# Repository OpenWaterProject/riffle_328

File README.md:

#Welcome!

This is a set of code and instructions for getting started with the Riffle_328 water monitor, version 0.1.8. 

- **QUICK START**.   If you already have experience using Arduino-compatible boards, you should probably just jump to the [Quick Start](https://github.com/dwblair/Riffle-Getting-Started#quick-start) section below to get up and running quickly. In general, the Riffle behaves like an Arduino UNO in the Arduino IDE (you should select "Arduino UNO" as the "Board" in the IDE), but you'll need to install a **special driver** (see [Software prep](test), below) in order to program the device over USB if you're using Mac or Windows.  

- **STEP-BY-STEP**.  If you would prefer more detailed instructions for setting up your Riffle, please check out the [Step-by-Step Instructions](./step-by-step.markdown).

- **EXAMPLES**. If you'd like to try out some example Riffle sensor applications (temperature, pressure, etc) in the [wiki](https://github.com/dwblair/Riffle-Getting-Started/wiki) of this repository (add your own!).

- **DESIGN PHILOSOPHY**.  A brief description of the motivation behind the design of the Riffle can be found [here](https://github.com/OpenWaterProject/riffle/blob/master/design_philosophy.md).  

# How you can contribute

Some useful guidelines about the best way to contribute to the project (or to fork it) can be found [here](contributing.md).

# Support and Licensing 

The Riffle_328 project has been supported through [Public Lab](www.publiclab.org)'s Open Water Initiative, and is licensed under [CERN OHL 1.2](LiCENSE.md).

# Quick Overview

**Hardware notes**.  This repository contains the design files and Bill of Materials for the Riffle water monitor.  The Riffle_328 is directly compatible with the Arduino IDE (it can be programmed as an "Arduino UNO" board).  The Riffle_328 ver 0.1.8 has the following features:

- Programmed as an "UNO" in the Arduino IDE
- Uses an Atmel 328p chip, running at 16 MHz and 3.3V.
- On-board microSD card
- On-board Serial-USB conversion using the CH340 chip.
- Battery measurement circuit
- High-precision, temperature-compensated RTC, the DS3221, with a CR1220 backup battery to maintain the time.
- Two power inputs, 3.5 - 6V.  -- one allows for Lithium-Ion charging when the Riffle is plugged into USB, the other is for extended, low-power operation. 
- It has additional on-board EEPROM memory, accessible via the I2C bus.
- It has MOSFET switches that can power down the microSD card, the external sensor power, and the battery measurement circuitry. 
- Analog pins, Digital pins, Power, Ground, Battery voltage, and I2C and SPI buses are broken out on a 2x7 header at the end of the board, as follows:

**Versions of the Riffle**. [Ben Gamari](https://github.com/bgamari)'s original [Riffle design](https://github.com/bgamari/riffle) is based on an ARM Cortex-M4 chip, the Kinetis K20.  The K20 is a more powerful chip than the Atmel 328, but the K20 version of the Riffle doesn't currently have firmware compatible with the Arduino IDE.  The Riffle_328 design covered in this repository is intended to be as directly compatible with the Arduino IDE as possible.

**Finding more resources**. The Riffle has been developed through many contributions by members of the [Public Lab](http://publiclab.org) community.  For more information, see:

- The main [Public Lab Riffle wiki](https://publiclab.org/wiki/riffle);
- All [posts and research notes](https://publiclab.org/search/riffle) related to the Riffle on Public Lab;
- The [Public Lab Water Quality Mailing list](https://groups.google.com/forum/#!forum/plots-waterquality).

# Quick Start

## Hardware prep

- For basic datalogging, ou'll need a Riffle board, a 3-6 volt battery (3.7 V Lithium Ion battery shown), and CR1220 coin cell battery.  Protoboards (shown) are optional. 

- Insert a microSD card and a CR1220 coin cell into the appropriate slots on the Riffle.

- The Riffle 328 ver 0.1.8 has two JST connectors for power inputs, a switch to choose between the two power inputs, and an indicator LED in the middle of the board (connected to pin 9):

- Insert a lithium ion battery into the 'Lith/USB' JST connector (JST connector labels are on the back side of the board).

- Make sure that the switch on the Riffle is switched to the side labeled 'Lith/USB' (label is next to switch).

- When you're done, your setup should look like this:

## Software prep

- Make sure that the Arduino IDE (version 1.6.10 or higher) is installed.  If it
 isn't, get it [here](https://www.arduino.cc/en/Main/Software).

- **Installing the USB-Serial Driver**. On Mac or Windows, the Riffle requires a special driver in order to be programmed via the Arduino IDE, due to the onbaord CH340 USB-Serial chip.  For Windows, you can use the driver [here]( http://raysfiles.com/drivers/ch341ser.exe).  For Mac, follow instructions [here]( http://www.instructables.com/id/Arduino-Nano-CH340/). Linux systems should generally not require additional drivers.

- Copy all of the folders in 'arduino_libraries' into the 'libraries' folder inside the 'sketchbook' folder associated with the Arduino IDE install.  These libraries are necessary for running the 'temp_logger.ino' and 'set_rtc.ino' sketches in this repo.  

## Logging values to the microSD card

- Using the Arduino IDE, compile the 'temp_logger.ino' code from the "example_sketches" folder in this repo, and load it onto the Riffle board, using 'Arduino UNO' as the 'Board' version in the Arduino IDE.

- The Riffle should start logging temperature values to the microSD card. These temperature values come from the on-board RTC, and so may be affected by the temeprature of the board (which might slightly higher than ambient temperature, due to the operation of its circuitry). 

- Note: the RTC will have its time set automatically to the system clock when it is programmed via the Arduino IDE.

## Extending the battery lifetime

- Set DEBUG = 0 in temp_logger.ino. This will reduce power by turning off the Serial interface.  It will also mean that the RTC is not set by the System clock.

- Use the 'GEN' JST connector on the Riffle board.  This power input doesn't have a protective diode, thus avoiding a diode-associated voltage drop, and can power the Riffle down to lower battery voltages.

- Test out different microSD cards;  some of them 'sleep' at lower power settings than others.

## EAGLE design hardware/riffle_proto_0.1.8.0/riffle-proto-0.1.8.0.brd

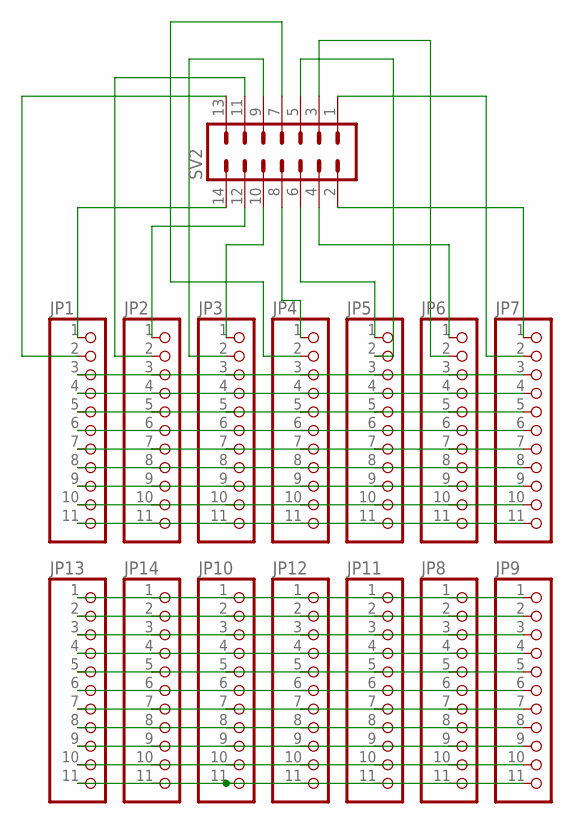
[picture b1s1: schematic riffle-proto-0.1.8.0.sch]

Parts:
JP1, JP2, JP3, JP4, JP5, JP6, JP7, JP8, JP9, JP10, JP11, JP12, JP13, JP14: HEADER-1X1176MIL; 1X11_ROUND_76
SV2: MA07-2

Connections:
unnamed: JP1.1, SV2.14
unnamed: JP2.1, SV2.12
unnamed: JP3.1, SV2.10
unnamed: JP4.1, SV2.8
unnamed: JP5.1, SV2.6
unnamed: JP6.1, SV2.4
unnamed: JP7.1, SV2.2
unnamed: JP1.2, SV2.13
unnamed: JP2.2, SV2.11
unnamed: JP3.2, SV2.9
unnamed: JP4.2, SV2.7
unnamed: JP5.2, SV2.5
unnamed: JP6.2, SV2.3
unnamed: JP7.2, SV2.1
unnamed: JP1.3, JP2.3, JP3.3, JP4.3, JP5.3, JP6.3, JP7.3
unnamed: JP1.4, JP2.4, JP3.4, JP4.4, JP5.4, JP6.4, JP7.4
unnamed: JP1.5, JP2.5, JP3.5, JP4.5, JP5.5, JP6.5, JP7.5
unnamed: JP1.6, JP2.6, JP3.6, JP4.6, JP5.6, JP6.6, JP7.6
unnamed: JP1.7, JP2.7, JP3.7, JP4.7, JP5.7, JP6.7, JP7.7
unnamed: JP1.8, JP2.8, JP3.8, JP4.8, JP5.8, JP6.8, JP7.8
unnamed: JP1.9, JP2.9, JP3.9, JP4.9, JP5.9, JP6.9, JP7.9
unnamed: JP1.10, JP2.10, JP3.10, JP4.10, JP5.10, JP6.10, JP7.10
unnamed: JP1.11, JP2.11, JP4.11, JP5.11, JP6.11, JP7.11
unnamed: JP8.1, JP9.1, JP10.1, JP11.1, JP12.1, JP13.1, JP14.1
unnamed: JP8.2, JP9.2, JP10.2, JP11.2, JP12.2, JP13.2, JP14.2
unnamed: JP8.3, JP9.3, JP10.3, JP11.3, JP12.3, JP13.3, JP14.3
unnamed: JP8.4, JP9.4, JP10.4, JP11.4, JP12.4, JP13.4, JP14.4
unnamed: JP8.5, JP9.5, JP10.5, JP11.5, JP12.5, JP13.5, JP14.5
unnamed: JP8.6, JP9.6, JP10.6, JP11.6, JP12.6, JP13.6, JP14.6
unnamed: JP8.7, JP9.7, JP10.7, JP11.7, JP12.7, JP13.7, JP14.7
unnamed: JP8.8, JP9.8, JP10.8, JP11.8, JP12.8, JP13.8, JP14.8
unnamed: JP8.9, JP9.9, JP10.9, JP11.9, JP12.9, JP13.9, JP14.9
unnamed: JP8.10, JP9.10, JP10.10, JP11.10, JP12.10, JP13.10, JP14.10
unnamed: JP8.11, JP9.11, JP10.11, JP11.11, JP12.11, JP13.11, JP14.11

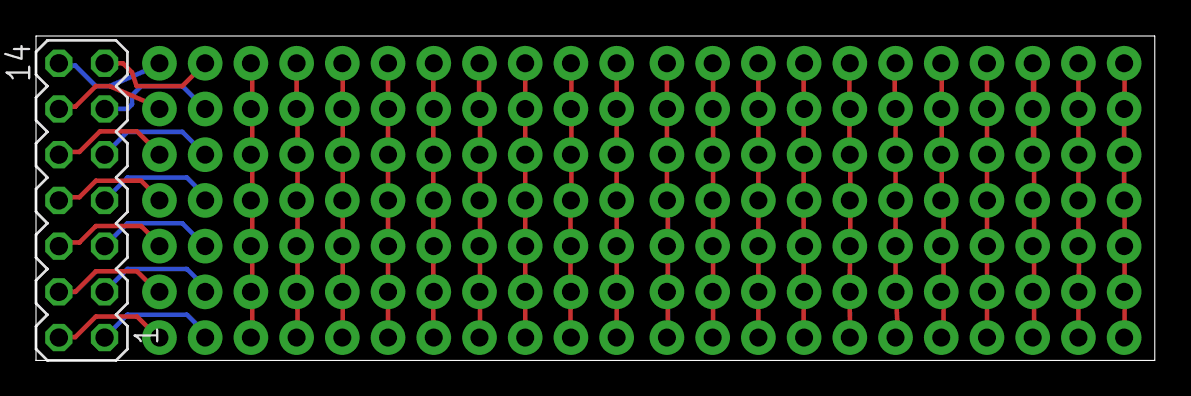
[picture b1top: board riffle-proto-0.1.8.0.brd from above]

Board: 2 copper layers, 62.2 x 18.0 mm, 15 parts (0 on the bottom side), 34 nets.

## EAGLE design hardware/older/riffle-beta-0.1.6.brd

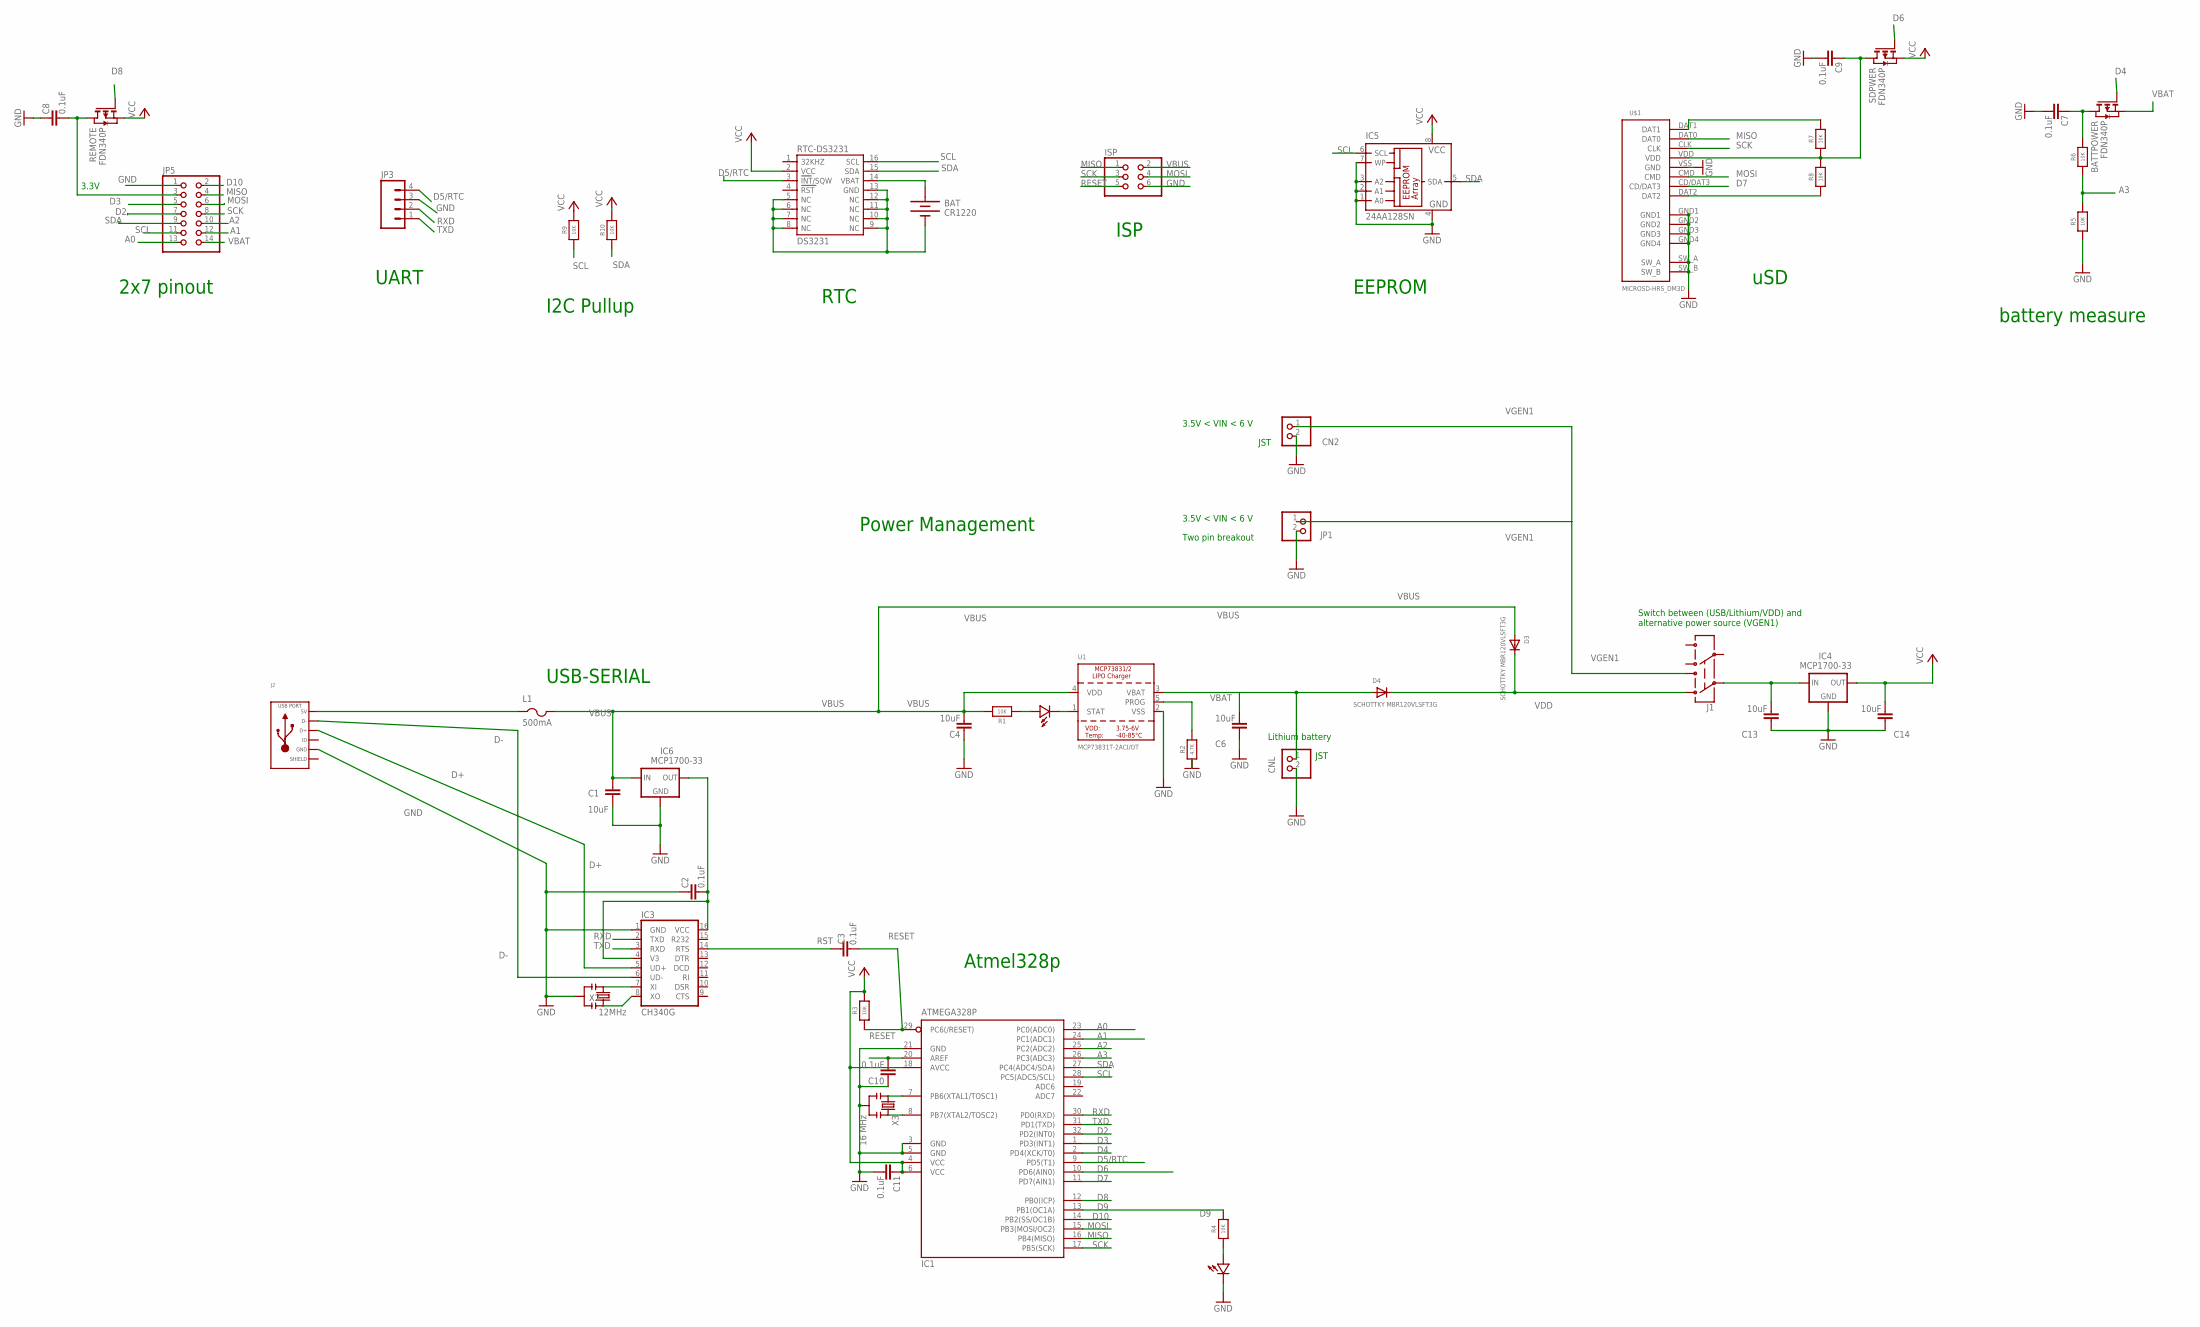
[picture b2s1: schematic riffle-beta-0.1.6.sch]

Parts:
BAT: CR1220; BATTCON_12MM_SMT
BATTPOWER: FDN340P; SOT-23
C1, C4, C6, C13, C14: 10uF; 0603-CAP
C2, C3, C7, C8, C9, C10, C11: 0.1uF; 0603-CAP
CN2: JST_2PIN-SMT-RA; JST-PH-2-SMT-RA
CNL: JST_2PIN-SMT-RA; JST-PH-2-SMT-RA
D1, D2: LED0603; 0603-LED
D3, D4: SCHOTTKY MBR120VLSFT3G; SOD-123FL
IC1: ATMEGA328P; TQFP32-08
IC3: CH340G; SO16
IC4, IC6: MCP1700-33; SOT89
IC5: 24AA128SN; SO-08
ISP: PINHD-2X3; 2X03
J1: AYZ0202
J2: USB_MICRO_RIGHT; MICROUSB-RIGHT
JP1: PINHD-1X2; 1X02
JP3: M04SMD; 1X04-SMD
JP5: PINHD-2X7; 2X07
L1: 500mA; R1206
R1, R3, R4, R5, R6, R7, R8, R9, R10: 10K; 0603-NO
R2: 4.7K; 0603-NO
REMOTE: FDN340P; SOT-23
RTC-DS3231: DS3231
SDPWER: FDN340P; SOT-23
U1: MCP73831T-2ACI/OT; SOT23-5
U$1: MICROSD-HRS_DM3D; DM3D
X2: 12MHz; RESONATOR-SMD
X3: 16 MHz; RESONATOR-SMD

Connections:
A0: IC1.23 (PC0(ADC0)), JP5.13
A1: IC1.24 (PC1(ADC1)), JP5.12
A2: IC1.25 (PC2(ADC2)), JP5.10
A3: IC1.26 (PC3(ADC3)), R5.2, R6.1
AREF: C10.1, IC1.20 (AREF)
D2: IC1.32 (PD2(INT0)), JP5.7
D3: IC1.1 (PD3(INT1)), JP5.5
D4: BATTPOWER.3 (G), IC1.2 (PD4(XCK/T0))
D5/RTC: IC1.9 (PD5(T1)), JP3.4, RTC-DS3231.3 (INT/SQW)
D6: IC1.10 (PD6(AIN0)), SDPWER.3 (G)
D7: IC1.11 (PD7(AIN1)), U$1.CD/DAT3
D8: IC1.12 (PB0(ICP)), REMOTE.3 (G)
D9: IC1.13 (PB1(OC1A)), R4.2
D10: IC1.14 (PB2(SS/OC1B)), JP5.2
D+: IC3.5 (UD+), J2.3 (D+)
D-: IC3.6 (UD-), J2.2 (D-)
GND: BAT.P$1 (-), C1.1, C2.2, C4.2, C6.2, C7.1, C8.2, C9.1, C10.2, C11.1, C13.2, C14.2, CN2.2 (1), CNL.2 (1), D2.MINUS, IC1.3 (GND), IC1.5 (GND), IC1.21 (GND), IC3.1 (GND), IC4.1 (GND), IC5.1 (A0), IC5.2 (A1), IC5.3 (A2), IC5.4 (GND), IC5.7 (WP), IC6.1 (GND), ISP.6, J2.5 (GND), JP1.2, JP3.3, JP5.1, R2.1, R5.1, RTC-DS3231.5 (NC), RTC-DS3231.6 (NC), RTC-DS3231.7 (NC), RTC-DS3231.8 (NC), RTC-DS3231.9 (NC), RTC-DS3231.10 (NC), RTC-DS3231.11 (NC), RTC-DS3231.12 (NC), RTC-DS3231.13 (GND), U1.2 (VSS), U$1.GND1, U$1.GND2, U$1.GND3, U$1.GND4, U$1.SW_A, U$1.SW_B, U$1.VSS (GND), X2.2, X3.2
MISO: IC1.16 (PB4(MISO)), ISP.1, JP5.4, U$1.DAT0
MOSI: IC1.15 (PB3(MOSI/OC2)), ISP.4, JP5.6, U$1.CMD
unnamed: C13.1, IC4.2 (IN), J1.2
unnamed: IC1.7 (PB6(XTAL1/TOSC1)), X3.1
unnamed: IC1.8 (PB7(XTAL2/TOSC2)), X3.3
unnamed: C9.2, R7.1, R8.2, SDPWER.1 (D), U$1.VDD
unnamed: D1.MINUS, U1.1 (STAT)
unnamed: R2.2, U1.5 (PROG)
unnamed: C8.1, JP5.3, REMOTE.1 (D)
unnamed: C2.1, IC3.4 (V3), IC3.16 (VCC), IC6.3 (OUT)
unnamed: J2.1 (5V), L1.1
unnamed: IC3.7 (XI), X2.1
unnamed: IC3.8 (XO), X2.3
unnamed: BATTPOWER.1 (D), C7.2, R6.2
unnamed: R7.2, U$1.DAT1
unnamed: D2.PLUS, R4.1
unnamed: R8.1, U$1.DAT2
unnamed: D1.PLUS, R1.1
RESET: C3.1, IC1.29 (PC6(/RESET)), ISP.5, R3.1
RST: C3.2, IC3.14 (RTS)
RTC_BATT: BAT.P$2 (+), RTC-DS3231.14 (VBAT)
RXD: IC1.30 (PD0(RXD)), IC3.2 (TXD), JP3.2
SCK: IC1.17 (PB5(SCK)), ISP.3, JP5.8, U$1.CLK
SCL: IC1.28 (PC5(ADC5/SCL)), IC5.6 (SCL), JP5.11, R9.1, RTC-DS3231.16 (SCL)
SDA: IC1.27 (PC4(ADC4/SDA)), IC5.5 (SDA), JP5.9, R10.1, RTC-DS3231.15 (SDA)
SLD: J2.S1 (SLD), J2.S2 (SLD), J2.S3 (SLD), J2.S4 (SLD), J2.S5 (SLD), J2.S6 (SLD), J2.S7 (SLD), J2.S8 (SLD)
TXD: IC1.31 (PD1(TXD)), IC3.3 (RXD), JP3.1
VBAT: BATTPOWER.2 (S), C6.1, CNL.1 (2), D4.A, JP5.14, U1.3 (VBAT)
VBUS: C1.2, C4.1, D3.A, IC6.2 (IN), ISP.2, L1.2, R1.2, U1.4 (VDD)
VCC: C11.2, C14.1, IC1.4 (VCC), IC1.6 (VCC), IC1.18 (AVCC), IC4.3 (OUT), IC5.8 (VCC), R3.2, R9.2, R10.2, REMOTE.2 (S), RTC-DS3231.2 (VCC), SDPWER.2 (S)
VDD: D3.C, D4.C, J1.3 (1)
VGEN1: CN2.1 (2), J1.1 (3), JP1.1

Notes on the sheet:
3.3V
USB-SERIAL
Atmel328p
Power Management
RTC
uSD
2x7 pinout
UART
I2C Pullup
ISP
EEPROM
battery measure
Lithium battery
3.5V < VIN < 6 V
JST
Two pin breakout
Switch between (USB/Lithium/VDD) and alternative power source (VGEN1)

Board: 2 copper layers, 49 parts (1 on the bottom side), 49 nets, no tracks yet.

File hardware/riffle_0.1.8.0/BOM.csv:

Part,Details,Device,Package,Description,,MF,Cost per 100,cost,Source
BAT,CR1220,BATTERYBATTERY_12MM_SMT,BATTCON_12MM_SMT,Battery Holders,,,1.8,1.8,http://www.digikey.com/product-detail/en/1056TR/1056KCT-ND/4772075
"BATTPOWER, REMOTE, SDPWER",FDN340P,PMOSSOT23,SOT-23,MOS FET,,,0.24,0.72,http://www.digikey.com/product-detail/en/FDN340P/FDN340PCT-N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
"C1,C4,C5,C6",10uF,CAP0603-CAP,0603-CAP,Capacitor,*,,0.07,0.28,http://www.digikey.com/product-detail/en/CC0603MRX5R5BB106/3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
"C2,C3,C7,C8,C9,C10,C11",0.1uF,CAP0603-CAP,0603-CAP,Capacitor,*,,0.04,0.28,http://www.digikey.com/product-detail/en/C0603C104J4RACTU/39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
CN1,,JST_2PIN-SMT-RA,JST-PH-2-SMT-RA,JST 2-Pin Connectors of various flavors,,,0.4,0.4,http://www.digikey.com/product-detail/en/S2B-PH-SM4-TB%28LF%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
D1,LED0603,LED0603,0603-LED,,*,blue,0.23,0.23,http://www.digikey.com/product-detail/en/APT1608QBC%2FD/754-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
D2,LED0603,LED0603,0603-LED,,,yellow,0.17,0.17,http://www.digikey.com/product-detail/en/APT1608SYCK/754-112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
"D3, D4",SCHOTTKY,DIODE_SOD-123FL,SOD-123FL,Diode,,,0.22,0.44,http://www.digikey.com/product-detail/en/SM4002PL-TP/SM4002P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
IC1,ATMEGA328P,MEGA8-AI,TQFP32-08,MICROCONTROLLER,*,ATMEGA8-16AU,2.7,2.7,http://www.digikey.com/product-detail/en/ATMEGA328P-AU/ATMEG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
IC2,MCP73831,MCP73831,SOT23-5,Microchip's MCP73831,,,0.42,0.42,http://www.digikey.com/product-detail/en/MCP73831T-2ACI%2FOT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
IC3,CH340G,CH340G,SO16,,,,0.6,0.6,rui
"IC4, IC6",MCP1700-33,MCP1700SOT89,SOT89,VOLTAGE REGULATOR,*,,0.29,0.58,http://www.digikey.com/product-detail/en/0/MCP1700T3302EMBCT-ND
IC5,24AA128SN,24AA128SN,SO-08,Serial EEPROM,,24AA128-I/SN,0.5,0.5,http://www.digikey.com/product-detail/en/24AA128-I%2FSN/24AA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
ISP,,PINHD-2X3,2X03,PIN HEADER,,,,,(leave open for programming)
J1,AYZ0202,AYZ0202,AYZ0202,SPDT Slide Switch,,,1.07,1.07,http://www.digikey.com/product-detail/en/AYZ0202AGRLC/401-20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
JP1,,PINHD-1X2,1X02,PIN HEADER,,,,,(leave open)
JP3,,M04SMD,1X04-SMD,Header 4,,,,,(leave open)
JP5,,PINHD-2X7,2X07,PIN HEADER,,,0.98,0.98,http://www.digikey.com/product-detail/en/PPTC072LJBN-RC/S552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
L1,500mA,PTCFUSE-1206,R1206,"PTC fuses, resettable thermistors",,,0.17,0.17,http://www.digikey.com/product-detail/en/0ZCA0050FF2G/507-14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
"R1,R3,R4,R5,R6,R9,R10",10K,RESISTOR_0603_NOOUT,0603-NO,Resistors,*,,0.02,0.14,http://www.digikey.com/product-detail/en/CR0603-JW-103GLF/CR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
R2,4.7K,RESISTOR_0603_NOOUT,0603-NO,Resistors,*,,0.11,0.11,http://www.digikey.com/product-detail/en/MCT0603MD4701DP500/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
"R7,R8",50K,RESISTOR_0603_NOOUT,0603-NO,Resistors,*,,0.005,0.01,http://www.digikey.com/product-detail/en/RC0603JR-07100RL/31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
RTC-DS3231,DS3231,DS3231,DS3231,,,,6.3,6.3,http://www.digikey.com/product-detail/en/DS3231S%23/DS3231S%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
U$1,MICROSD-HRS_DM3D,MICROSD-HRS_DM3D,DM3D,,*,,1.5,1.5,http://www.digikey.com/product-detail/en/DM3D-SF/HR1941CT-ND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
U$4,,"USB-AB""",USB-AB-MICRO-SMD_V02_BOSS,This is a USB AB connector that is compatible with USB OTG. i.e. this connector can serve as a host or device,,,0.6,0.6,http://www.digikey.com/product-detail/en/10104111-0001LF/609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
X2,12MHz,RESONATORSMD,RESONATOR-SMD,Resonator,,X,0.4,0.4,https://www.digikey.com/product-detail/en/CSTCE12M0G55-R0/49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
X3,16 MHz,RESONATORSMD,RESONATOR-SMD,Resonator,*,,0.32,0.32,http://www.digikey.com/product-detail/en/CSTCE16M0V53-R0/490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

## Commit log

2015-07-19 added mac driver to readme
2015-07-19 added sdcard test
2015-07-19 added more test code
2015-07-20 updated tests and readme
2015-07-20 updated readme for typo, clarity
2015-09-08 added pinout images for 0.96
2015-09-10 fix USB driver link in software README
2016-01-05 Add Gitter badge
2016-01-07 fixed IC2 footprint from 6 to 5 pins
2016-01-12 tightened USB cutout; moved via away from left screw
2016-01-12 added +/- artwork
2016-01-23 fixed switch; added diodes
2016-01-23 cleaned up schematic
2016-01-23 routed board
2016-01-23 uupdate
2016-01-23 added fuse and VBUS diode

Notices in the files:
hardware/older/riffle-beta-0.1.6.brd:
CERN OHL v1.2
parts and their libraries:
microbuilder: This work is placed in the public domain, and may be freely used for commercial and non-commercial work with the following conditions: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
